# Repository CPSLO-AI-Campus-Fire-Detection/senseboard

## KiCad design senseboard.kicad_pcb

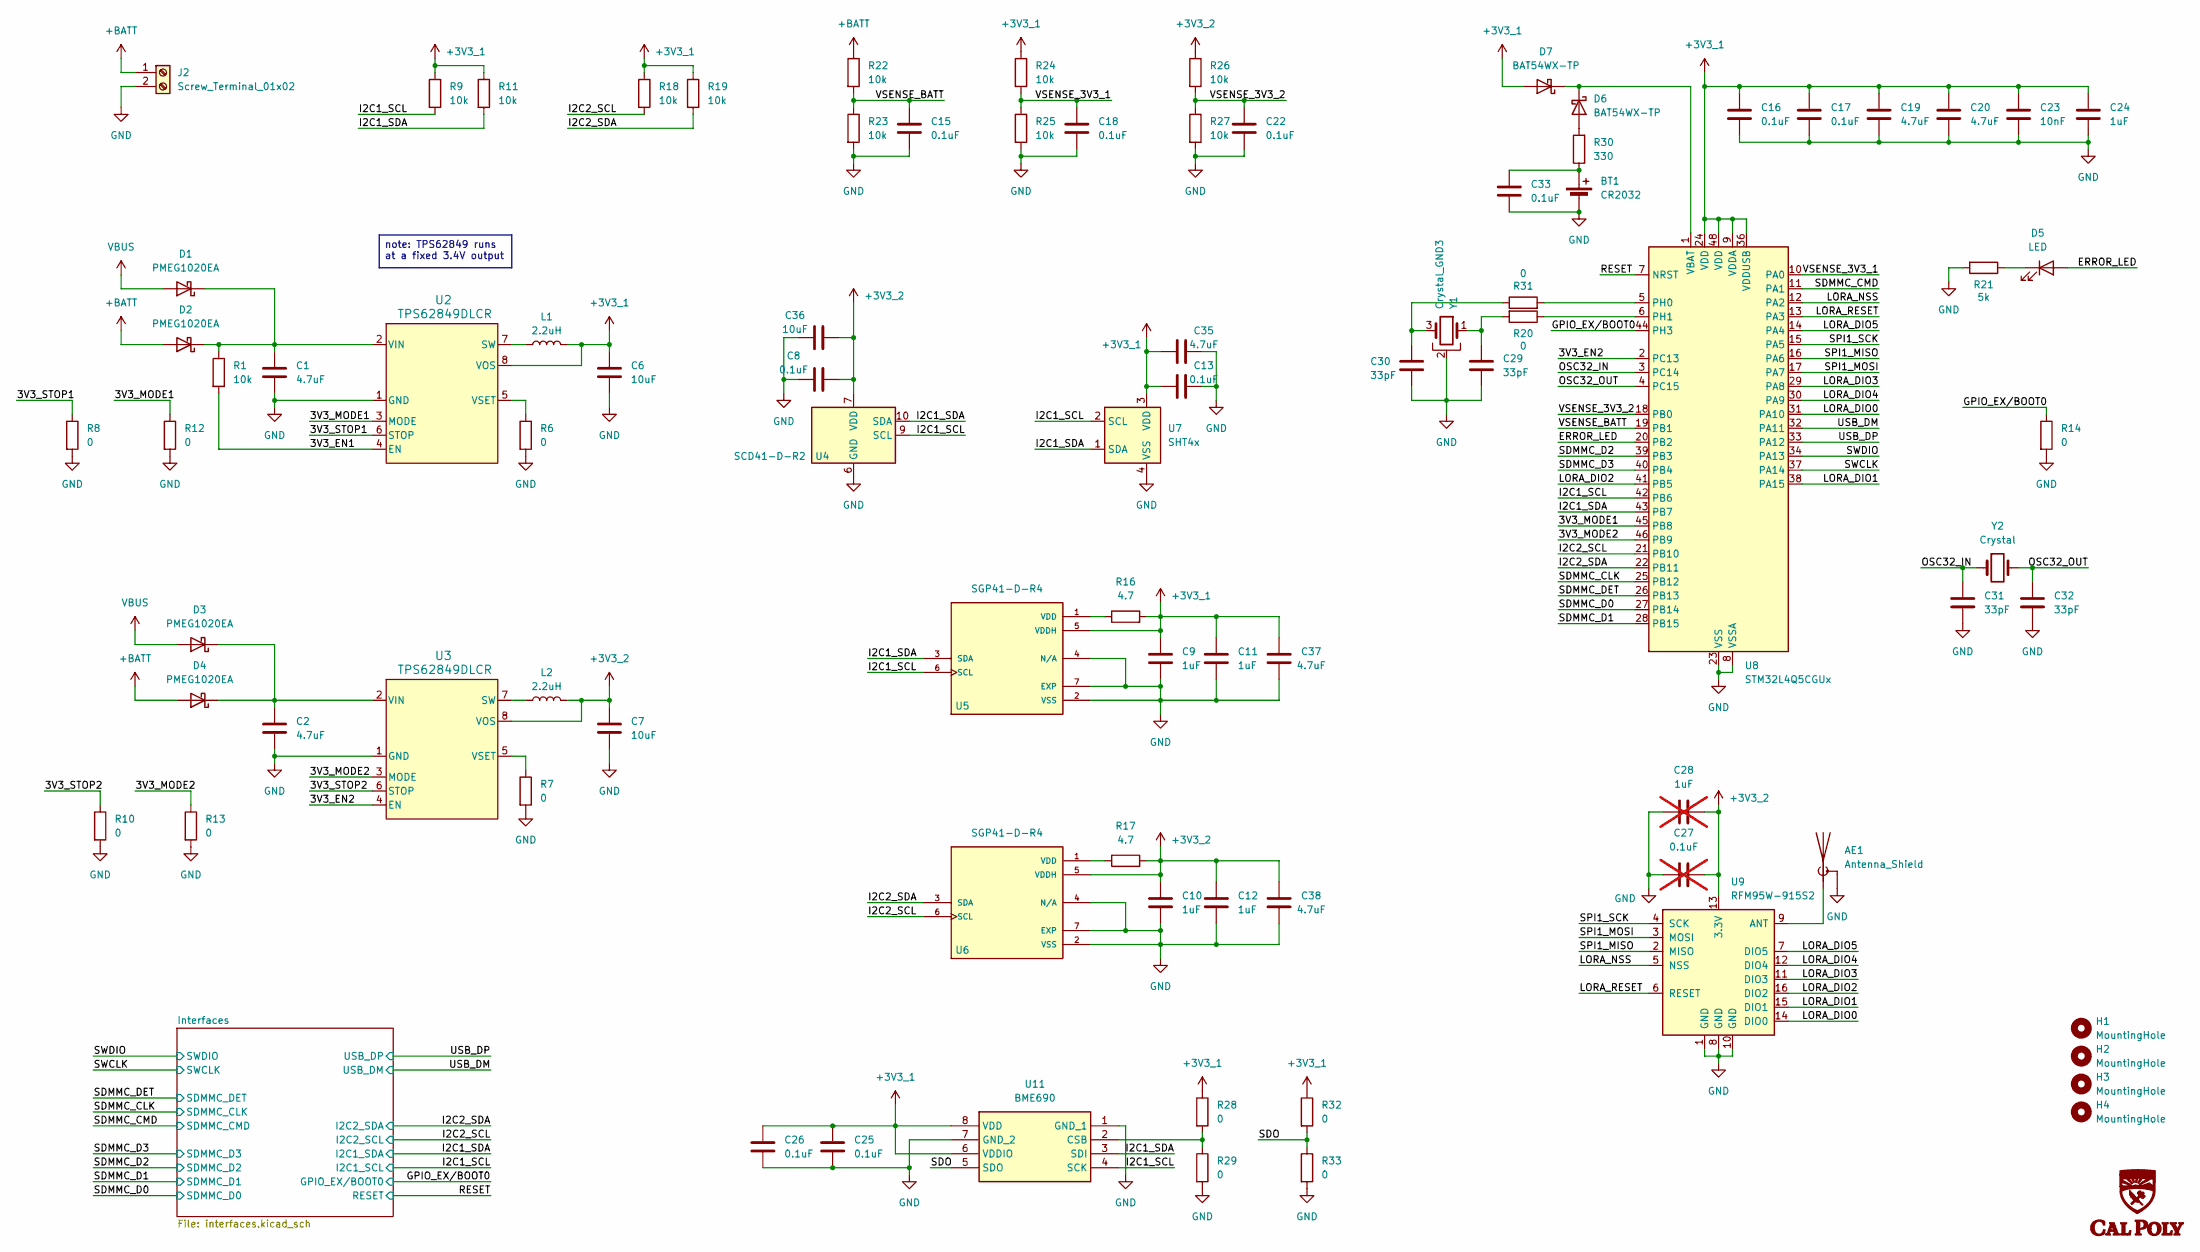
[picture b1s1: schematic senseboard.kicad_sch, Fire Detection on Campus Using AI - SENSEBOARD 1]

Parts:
AE1: Antenna_Shield; SMA_Molex_73251-1153_EdgeMount_Horizontal
BT1: CR2032; BatteryHolder_Keystone_1057_1x2032
C1, C2: 4.7uF; C_0805_2012Metric
C6, C7, C36: 10uF; C_0805_2012Metric
C8, C13, C15, C16, C17, C18, C22, C25, C26, C33: 0.1uF; C_0402_1005Metric
C9, C10, C11, C12, C24: 1uF; C_0603_1608Metric
C19, C20, C35, C37, C38: 4.7uF; C_0603_1608Metric
C23: 10nF; C_0402_1005Metric
C27: 0.1uF; C_0603_1608Metric; not fitted
C28: 1uF; C_0805_2012Metric; not fitted
C29, C30, C31, C32: 33pF; C_0402_1005Metric
D1, D3: PMEG1020EA; D_SMP_DO-220AA
D2, D4: PMEG1020EA; D_SMA
D5: LED; LED_0402_1005Metric
D6, D7: BAT54WX-TP; D_SOD-523
H1, H2, H3, H4: MountingHole; MountingHole_3.2mm_M3_ISO7380
J2: Screw_Terminal_01x02; JST_XH_B2B-XH-AM_1x02_P2.50mm_Vertical
L1, L2: 2.2uH; L_Murata_DFE201610P
R1, R9, R11, R18, R19, R22, R23, R24, R25, R26, R27: 10k; R_0402_1005Metric
R6, R7, R8, R10, R12, R13, R14, R20, R28, R29, R31, R32, R33: 0; R_0402_1005Metric
R16, R17: 4.7; R_0603_1608Metric
R21: 5k; R_0402_1005Metric
R30: 330; R_0603_1608Metric
U2, U3: TPS62849DLCR; VSON8_2P1X1P6_TEX
U4: SCD41-D-R2; Sensirion_SCD4x-1EP_10.1x10.1mm_P1.25mm_EP4.8x4.8mm
U5, U6: SGP41-D-R4; XDCR_SGP41-D-R4; PARTREV 1.0
U7: SHT4x; Sensirion_DFN-4_1.5x1.5mm_P0.8mm_SHT4x_NoCentralPad
U8: STM32L4Q5CGUx; QFN-48-1EP_7x7mm_P0.5mm_EP5.6x5.6mm
U9: RFM95W-915S2; HOPERF_RFM9XW_SMD
U11: BME690; Mouser Part Number 262-BME690
Y1: Crystal_GND3; Resonator_SMD_Murata_CSTxExxV-3Pin_3.0x1.1mm
Y2: Crystal; Crystal_SMD_EuroQuartz_EQ161-2Pin_3.2x1.5mm

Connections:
+3V3_1: C6.1, C9.2, C11.2, C13.2, C16.2, C17.2, C19.2, C20.2, C23.2, C24.2, C25.1, C26.1, C35.2, C37.1, D7.2 (A), L1.2, R9.1, R11.1, R16.2, R18.1, R19.1, R24.1, R28.1, R32.1, U2.8 (VOS), U5.5 (VDDH), U7.3 (VDD), U8.9 (VDDA), U8.24 (VDD), U8.36 (VDDUSB), U8.48 (VDD), U11.6 (VDDIO), U11.8 (VDD); also elsewhere on the board
+3V3_2: C7.1, C8.2, C10.2, C12.2, C27.1, C28.1, C36.2, C38.1, L2.2, R17.2, R26.1, U3.8 (VOS), U4.7 (VDD), U4.19 (VDD), U6.5 (VDDH), U9.13 (3.3V)
+BATT: D2.2 (A), D4.2 (A), J2.1, R22.1
/3V3_EN1: R1.2, U2.4 (EN)
/3V3_EN2: U3.4 (EN), U8.2 (PC13)
/3V3_MODE1: R12.1, U2.3 (MODE), U8.45 (PB8)
/3V3_MODE2: R13.1, U3.3 (MODE), U8.46 (PB9)
/3V3_STOP1: R8.1, U2.6 (STOP)
/3V3_STOP2: R10.1, U3.6 (STOP)
/ERROR_LED: D5.2 (A), U8.20 (PB2)
/GPIO_EX/BOOT0: R14.1, U8.44 (PH3); also elsewhere on the board
/I2C1_SCL: R9.2, U4.9 (SCL), U5.6 (SCL), U7.2 (SCL), U8.42 (PB6), U11.4 (SCK); also elsewhere on the board
/I2C1_SDA: R11.2, U4.10 (SDA), U5.3 (SDA), U7.1 (SDA), U8.43 (PB7), U11.3 (SDI); also elsewhere on the board
/I2C2_SCL: R18.2, U6.6 (SCL), U8.21 (PB10); also elsewhere on the board
/I2C2_SDA: R19.2, U6.3 (SDA), U8.22 (PB11); also elsewhere on the board
/LORA_DIO0: U8.31 (PA10), U9.14 (DIO0)
/LORA_DIO1: U8.38 (PA15), U9.15 (DIO1)
/LORA_DIO2: U8.41 (PB5), U9.16 (DIO2)
/LORA_DIO3: U8.29 (PA8), U9.11 (DIO3)
/LORA_DIO4: U8.30 (PA9), U9.12 (DIO4)
/LORA_DIO5: U8.14 (PA4), U9.7 (DIO5)
/LORA_NSS: U8.12 (PA2), U9.5 (NSS)
/LORA_RESET: U8.13 (PA3), U9.6 (RESET)
/OSC32_IN: C31.1, U8.3 (PC14), Y2.1
/OSC32_OUT: C32.1, U8.4 (PC15), Y2.2
/RESET: U8.7 (NRST); also elsewhere on the board
/SDMMC_CLK: U8.25 (PB12); also elsewhere on the board
/SDMMC_CMD: U8.11 (PA1); also elsewhere on the board
/SDMMC_D0: U8.27 (PB14); also elsewhere on the board
/SDMMC_D1: U8.28 (PB15); also elsewhere on the board
/SDMMC_D2: U8.39 (PB3); also elsewhere on the board
/SDMMC_D3: U8.40 (PB4); also elsewhere on the board
/SDMMC_DET: U8.26 (PB13); also elsewhere on the board
/SDO: R32.2, R33.1, U11.5 (SDO)
/SPI1_MISO: U8.16 (PA6), U9.2 (MISO)
/SPI1_MOSI: U8.17 (PA7), U9.3 (MOSI)
/SPI1_SCK: U8.15 (PA5), U9.4 (SCK)
/SWCLK: U8.37 (PA14); also elsewhere on the board
/SWDIO: U8.34 (PA13); also elsewhere on the board
/USB_DM: U8.32 (PA11); also elsewhere on the board
/USB_DP: U8.33 (PA12); also elsewhere on the board
/VSENSE_3V3_1: C18.1, R24.2, R25.1, U8.10 (PA0)
/VSENSE_3V3_2: C22.1, R26.2, R27.1, U8.18 (PB0)
/VSENSE_BATT: C15.1, R22.2, R23.1, U8.19 (PB1)
GND: AE1.2 (Shield), BT1.2 (-), C1.2, C2.2, C6.2, C7.2, C8.1, C9.1, C10.1, C11.1, C12.1, C13.1, C15.2, C16.1, C17.1, C18.2, C19.1, C20.1, C22.2, C23.1, C24.1, C25.2, C26.2, C27.2, C28.2, C29.2, C30.1, C31.2, C32.2, C33.1, C35.1, C36.1, C37.2, C38.2, J2.2, R6.2, R7.2, R8.2, R10.2, R12.2, R13.2, R14.2, R21.2, R23.2, R25.2, R27.2, R29.2, R33.2, U2.1 (GND), U3.1 (GND), U4.6 (GND), U4.20 (GND), U4.21 (GND), U5.2 (VSS), U5.4 (N/A), U5.7 (EXP), U6.2 (VSS), U6.4 (N/A), U6.7 (EXP), U7.4 (VSS), U8.8 (VSSA), U8.23 (VSS), U8.35 (VSS), U8.47 (VSS), U8.49 (VSS), U9.1 (GND), U9.8 (GND), U9.10 (GND), U11.1 (GND_1), U11.7 (GND_2), Y1.2; also elsewhere on the board
unnamed: AE1.1 (A), U9.9 (ANT)
unnamed: BT1.1 (+), C33.2, R30.1
unnamed: C29.1, R20.2, Y1.1
unnamed: C30.2, R31.1, Y1.3
unnamed: C1.1, D1.1 (K), D2.1 (K), R1.1, U2.2 (VIN)
unnamed: C2.1, D3.1 (K), D4.1 (K), U3.2 (VIN)
unnamed: D5.1 (K), R21.1
unnamed: D6.2 (A), R30.2
unnamed: D6.1 (K), D7.1 (K), U8.1 (VBAT)
unnamed: L1.1, U2.7 (SW)
unnamed: R6.1, U2.5 (VSET)
unnamed: L2.1, U3.7 (SW)
unnamed: R7.1, U3.5 (VSET)
unnamed: R16.1, U5.1 (VDD)
unnamed: R17.1, U6.1 (VDD)
unnamed: R31.2, U8.5 (PH0)
unnamed: R20.1, U8.6 (PH1)
unnamed: R28.2, R29.1, U11.2 (CSB)
VBUS: D1.2 (A), D3.2 (A); also elsewhere on the board

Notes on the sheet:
note: TPS62849 runs at a fixed 3.4V output

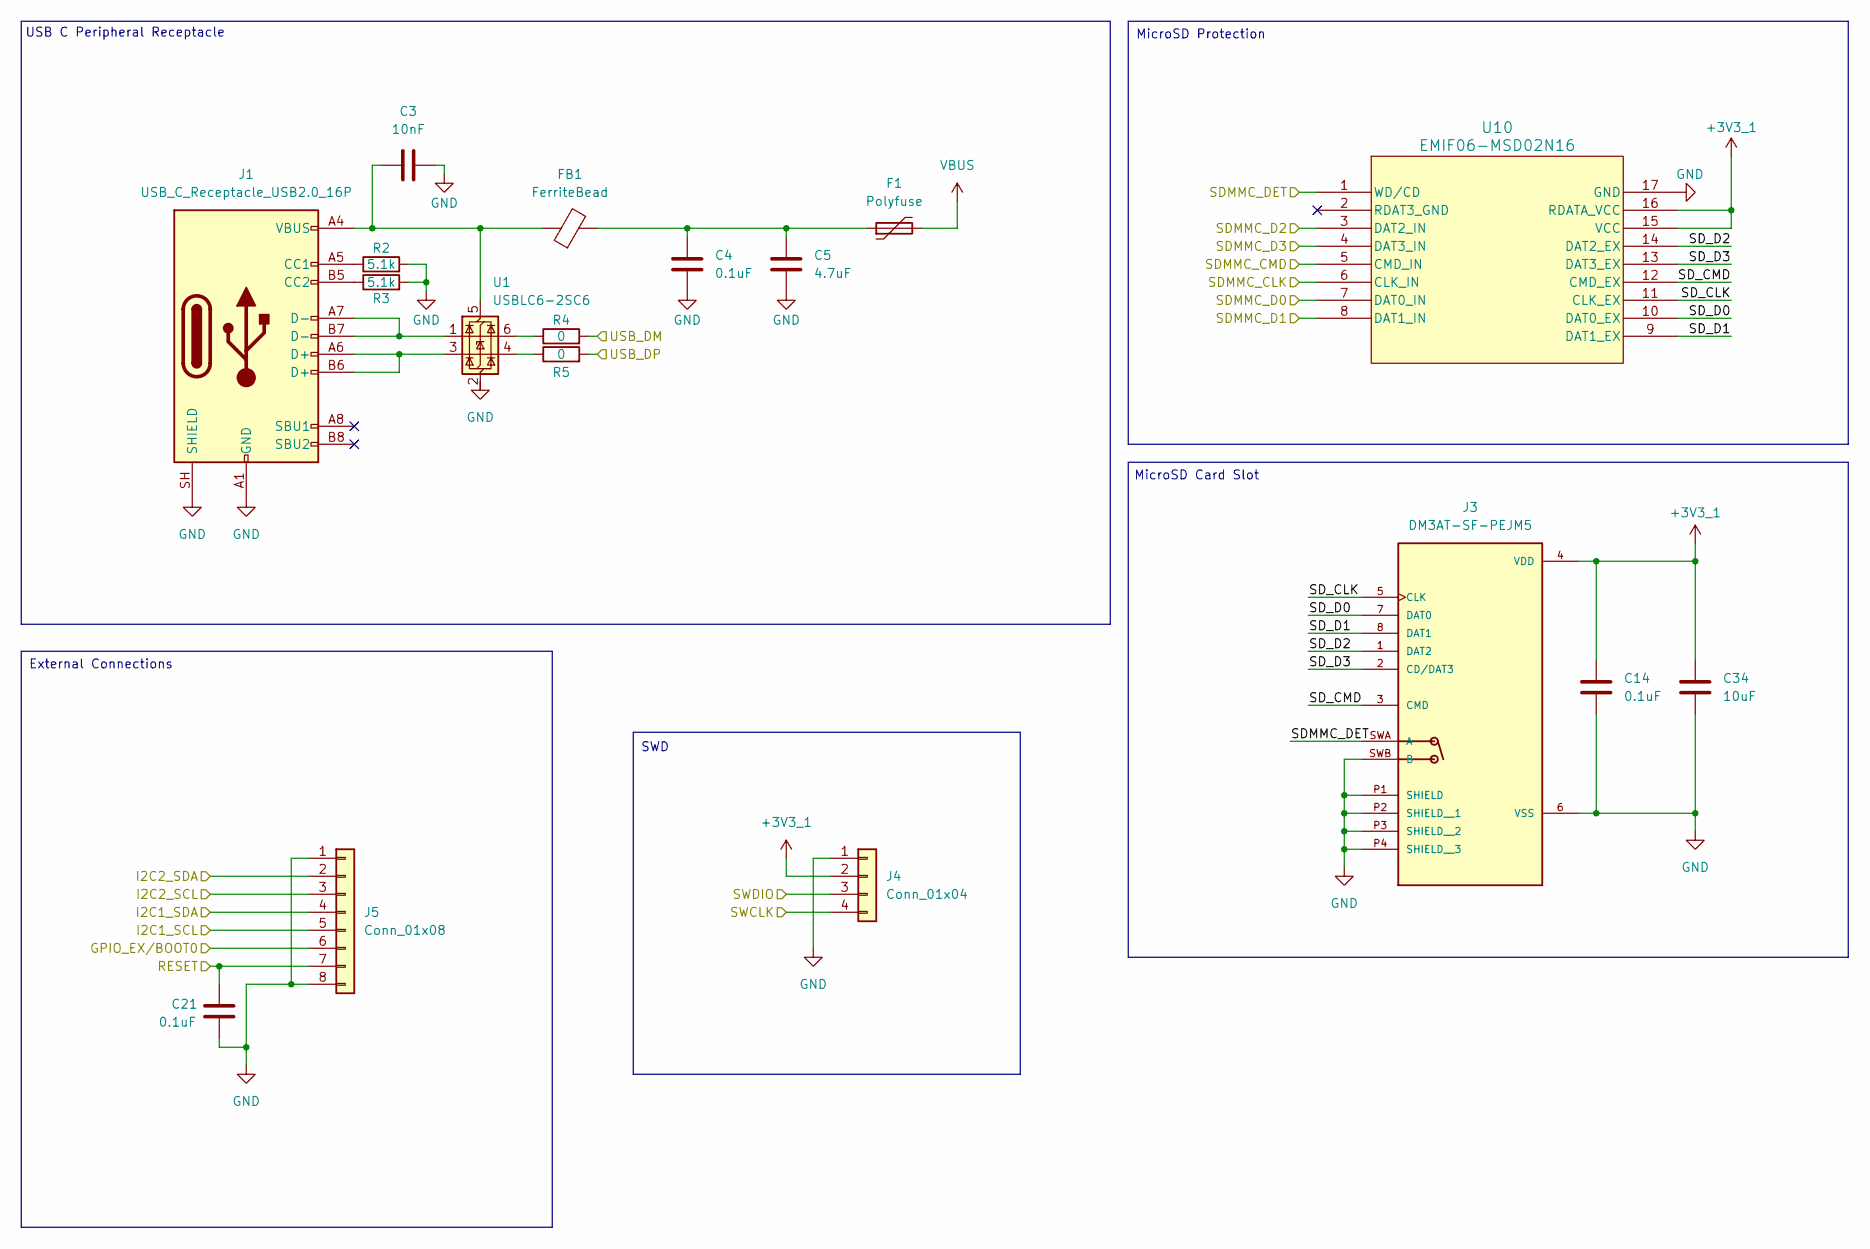
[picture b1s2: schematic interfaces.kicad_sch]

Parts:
C3: 10nF; C_0402_1005Metric
C4, C14, C21: 0.1uF; C_0402_1005Metric
C5: 4.7uF; C_0805_2012Metric
C34: 10uF; C_0805_2012Metric
F1: Polyfuse; Fuse_0805_2012Metric
FB1: FerriteBead; L_0603_1608Metric
J1: USB_C_Receptacle_USB2.0_16P; USB_C_Receptacle_G-Switch_GT-USB-7010ASV
J3: DM3AT-SF-PEJM5; HRS_DM3AT-SF-PEJM5; PARTREV 20200913
J4: Conn_01x04; PinHeader_1x04_P2.54mm_Vertical
J5: Conn_01x08; PinHeader_1x08_P2.54mm_Vertical
R2, R3: 5.1k; R_0402_1005Metric
R4, R5: 0; R_0402_1005Metric
U1: USBLC6-2SC6; SOT-23-6
U10: EMIF06-MSD02N16; MICROQFN16_1P25X3P55X0P4_STM

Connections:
+3V3_1: C14.1, C34.1, J3.4 (VDD), J4.2, U10.15 (VCC), U10.16 (RDATA_VCC); also elsewhere on the board
/GPIO_EX/BOOT0: J5.6; also elsewhere on the board
/I2C1_SCL: J5.5; also elsewhere on the board
/I2C1_SDA: J5.4; also elsewhere on the board
/I2C2_SCL: J5.3; also elsewhere on the board
/I2C2_SDA: J5.2; also elsewhere on the board
/Interfaces/SD_CLK: J3.5 (CLK), U10.11 (CLK_EX)
/Interfaces/SD_CMD: J3.3 (CMD), U10.12 (CMD_EX)
/Interfaces/SD_D0: J3.7 (DAT0), U10.10 (DAT0_EX)
/Interfaces/SD_D1: J3.8 (DAT1), U10.9 (DAT1_EX)
/Interfaces/SD_D2: J3.1 (DAT2), U10.14 (DAT2_EX)
/Interfaces/SD_D3: J3.2 (CD/DAT3), U10.13 (DAT3_EX)
/RESET: C21.1, J5.7; also elsewhere on the board
/SDMMC_CLK: U10.6 (CLK_IN); also elsewhere on the board
/SDMMC_CMD: U10.5 (CMD_IN); also elsewhere on the board
/SDMMC_D0: U10.7 (DAT0_IN); also elsewhere on the board
/SDMMC_D1: U10.8 (DAT1_IN); also elsewhere on the board
/SDMMC_D2: U10.3 (DAT2_IN); also elsewhere on the board
/SDMMC_D3: U10.4 (DAT3_IN); also elsewhere on the board
/SDMMC_DET: J3.SWA (A), U10.1 (WD/CD); also elsewhere on the board
/SWCLK: J4.4; also elsewhere on the board
/SWDIO: J4.3; also elsewhere on the board
/USB_DM: R4.2; also elsewhere on the board
/USB_DP: R5.2; also elsewhere on the board
GND: C3.2, C4.1, C5.1, C14.2, C21.2, C34.2, J1.A1 (GND), J1.A12 (GND), J1.B1 (GND), J1.B12 (GND), J1.SH (SHIELD), J3.6 (VSS), J3.P1 (SHIELD), J3.P2 (SHIELD__1), J3.P3 (SHIELD__2), J3.P4 (SHIELD__3), J3.SWB (B), J4.1, J5.1, J5.8, R2.2, R3.2, U10.17 (GND); also elsewhere on the board
unnamed: C4.2, C5.2, F1.1, FB1.2
unnamed: J1.A5 (CC1), R2.1
unnamed: J1.B5 (CC2), R3.1
unnamed: J1.A6 (D+), J1.B6 (D+), U1.3 (I/O2)
unnamed: J1.A7 (D-), J1.B7 (D-), U1.1 (I/O1)
unnamed: R4.1, U1.6 (I/O1)
unnamed: R5.1, U1.4 (I/O2)
unnamed: C3.1, FB1.1, J1.A4 (VBUS), J1.A9 (VBUS), J1.B4 (VBUS), J1.B9 (VBUS), U1.5 (VBUS)
VBUS: F1.2; also elsewhere on the board

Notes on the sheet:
External Connections
SWD
MicroSD Card Slot
MicroSD Protection
USB C Peripheral Receptacle

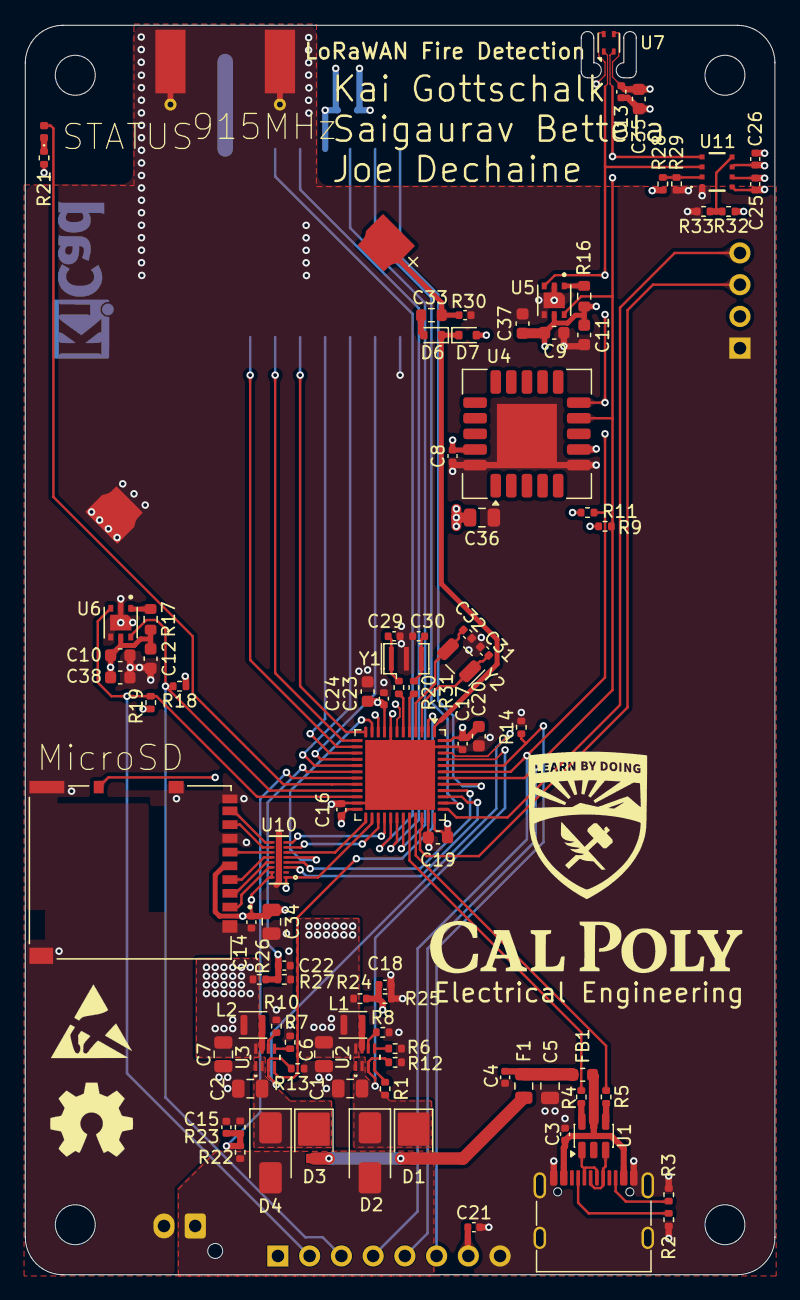
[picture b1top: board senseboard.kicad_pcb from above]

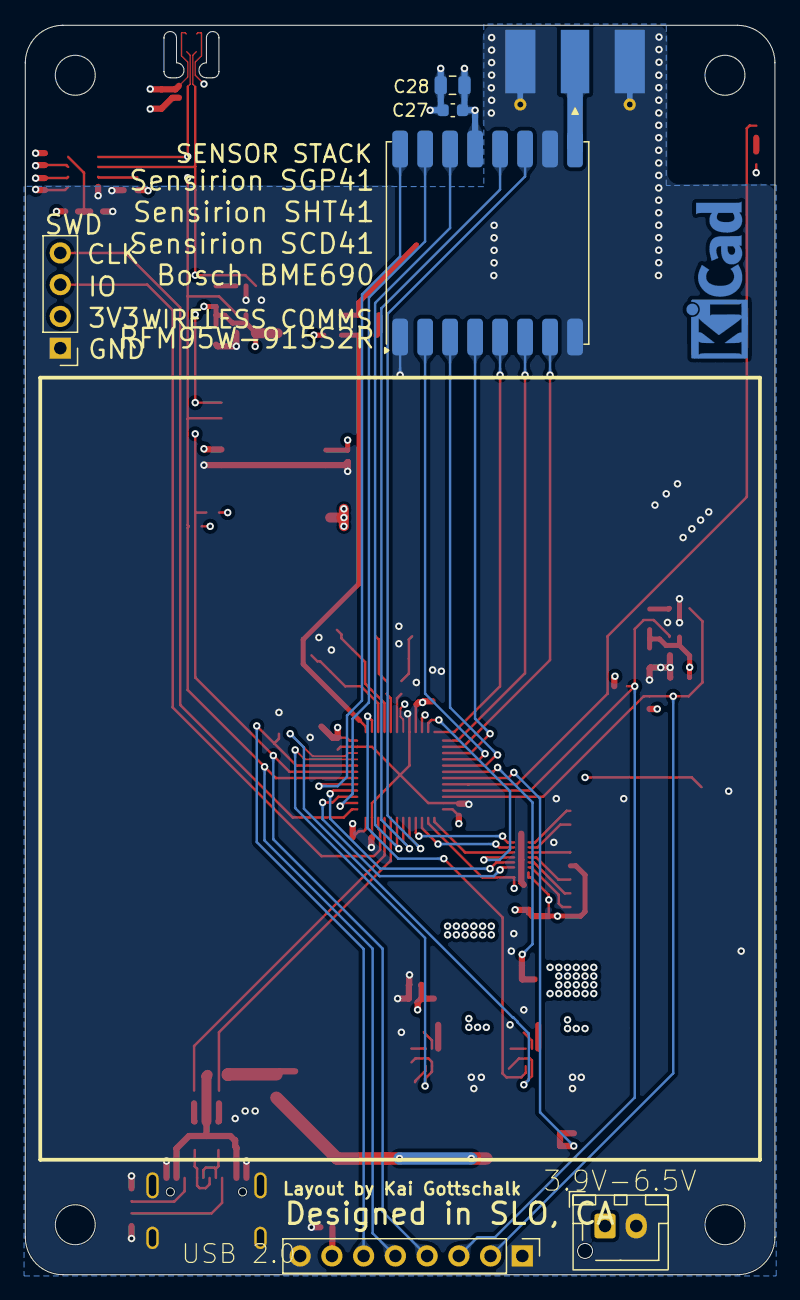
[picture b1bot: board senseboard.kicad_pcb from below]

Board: 6 copper layers, 60.0 x 100.0 mm, 105 parts (7 on the bottom side), 78 nets.

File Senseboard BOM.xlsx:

Value | Reference | Footprint | JLCPCB Part # | Qty | MFR | PN | DNP
DNP | AE1 | Connector_Coaxial:SMA_Molex_73251-1153_EdgeMount_Horizontal | DNP | 1 | Molex | 732511153 | DNP
DNP | BT1 | Battery:BatteryHolder_Keystone_1057_1x2032 | DNP | 1 | Keystone Electronics | 1057
4.7uF | C1,C2,C5 | Capacitor_SMD:C_0805_2012Metric | C1779 | 3 | Samsung Electro-Mechanics | CL21A475KAQNNNE
10nF | C3,C23 | Capacitor_SMD:C_0402_1005Metric | C327009 | 2 | Murata Electronics | GRM155R71C103KA01D
0.1uF | C4,C8,C13,C14,C15,C16,C17,C18,C21,C22,C25,C26,C33 | Capacitor_SMD:C_0402_1005Metric | C133086 | 13 | Samsung Electro-Mechanics | CL05B104KP5NNNC
10uF | C6,C7,C34,C36 | Capacitor_SMD:C_0805_2012Metric | C1713 | 4 | Samsung Electro-Mechanics | CL21A106KOQNNNE
1uF | C9,C10,C11,C12,C24 | Capacitor_SMD:C_0603_1608Metric | C29936 | 5 | Samsung Electro-Mechanics | CL10B105KA8NNNC
4.7uF | C19,C20,C35,C37,C38 | Capacitor_SMD:C_0603_1608Metric | C1705 | 5 | Samsung Electro-Mechanics | CL10A475KP8NNNC
DNP | C27 | Capacitor_SMD:C_0603_1608Metric |  | 1 | KEMET | C0603C104K3RACTU | DNP
DNP | C28 | Capacitor_SMD:C_0805_2012Metric |  | 1 | Samsung Electro-Mechanics | CL21A475KAQNNNE | DNP
DNP | C29,C30 | Capacitor_SMD:C_0402_1005Metric |  | 2 |  |  | DNP
7pF | C31,C32 | Capacitor_SMD:C_0402_1005Metric | C161333 | 2 | Murata Electronics | GRM1555C1H7R0CA01D
STPS120MF | D1,D3 | Diode_SMD:D_SMP_DO-220AA | C2927425 | 2 | STMicroelectronics | STPS120MF
STPS1L30A | D2,D4 | Diode_SMD:D_SMA | C157388 | 2 | STMicroelectronics | STPS1L30A
LED | D5 | LED_SMD:LED_0402_1005Metric | C364556 | 1 | Lite-On Inc. | LTST-C281KRKT
BAT54WX-TP | D6,D7 | Diode_SMD:D_SOD-523 | C283259 | 2 | MCC (Micro Commercial Components) | BAT54WX-TP
Polyfuse | F1 | Fuse:Fuse_0805_2012Metric | C5220829 | 1 | Bel Fuse Inc. | 0ZCK0050FF2E
FerriteBead | FB1 | Inductor_SMD:L_0603_1608Metric | C107335 | 1 | TDK | MPZ1608S601ATA00
USB_C_Receptacle_USB2.0_16P | J1 | Connector_USB:USB_C_Receptacle_G-Switch_GT-USB-7010ASV | C2988369 | 1 | G-Switch | GT-USB-7010ASV
DNP | J2 | Connector_JST:JST_XH_B2B-XH-AM_1x02_P2.50mm_Vertical |  | 1 | JST Sales America Inc. | B2B-XH-AM | DNP
DM3AT-SF-PEJM5 | J3 | DM3AT_SF_PEJM5:HRS_DM3AT-SF-PEJM5 | C114218 | 1 | Hirose Electric Co Ltd | DM3AT-SF-PEJM5
DNP | J4 | Connector_PinHeader_2.54mm:PinHeader_1x04_P2.54mm_Vertical |  | 1 |  |  | DNP
DNP | J5 | Connector_PinHeader_2.54mm:PinHeader_1x08_P2.54mm_Vertical |  | 1 |  |  | DNP
2.2uH | L1,L2 | Inductor_SMD:L_Murata_DFE201610P | C337893 | 2 | Murata Electronics | DFE201612E-2R2M=P2
10k | R1,R9,R11,R18,R19 | Resistor_SMD:R_0402_1005Metric | C60490 | 5 | YAGEO | RC0402FR-0710KL
5.1k | R2,R3 | Resistor_SMD:R_0402_1005Metric | C278598 | 2 | Panasonic Industry | ERJ-2RKF5101X
0 | R4,R5,R6,R7,R8,R10,R20,R28,R31,R33 | Resistor_SMD:R_0402_1005Metric | C60485 | 10 | YAGEO | RC0402JR-070RL
100k | R12,R13,R14 | Resistor_SMD:R_0402_1005Metric | C60491 | 3 | YAGEO | RC0402FR-07100KL
4.7 | R16,R17 | Resistor_SMD:R_0603_1608Metric | C5549523 | 2 | YAGEO | RC0603FR-134R7L
330 | R21 | Resistor_SMD:R_0402_1005Metric | C226996 | 1 | YAGEO | AC0402FR-07330RL
47k | R22,R23,R24,R25,R26,R27 | Resistor_SMD:R_0402_1005Metric | C728561 | 6 | YAGEO | RT0402BRD0747KL
DNP | R29,R32 | Resistor_SMD:R_0402_1005Metric |  | 2 | YAGEO | RC0402JR-070RL | DNP
330 | R30 | Resistor_SMD:R_0603_1608Metric | C105881 | 1 | YAGEO | RC0603FR-07330RL
USBLC6-2SC6 | U1 | Package_TO_SOT_SMD:SOT-23-6 | C7519 | 1 | STMicroelectronics | USBLC6-2SC6
TPS62849DLCR | U2,U3 | TPS62849DLCR:VSON8_2P1X1P6_TEX | C2071003 | 2 | Texas Instruments | TPS62849DLCR
SCD41-D-R2 | U4 | Sensor:Sensirion_SCD4x-1EP_10.1x10.1mm_P1.25mm_EP4.8x4.8mm | C3659294 | 1 | Sensirion AG | SCD41-D-R2
SGP41-D-R4 | U5,U6 | SGP41-D-R4:XDCR_SGP41-D-R4 | C3659325 | 2 | Sensirion AG | SGP41-D-R4
SHT4x | U7 | Sensor_Humidity:Sensirion_DFN-4_1.5x1.5mm_P0.8mm_SHT4x_NoCentralPad | C7461863 | 1 | Sensirion AG | SHT41A-FD1B-R2
STM32L4Q5CGUx | U8 | Package_DFN_QFN:QFN-48-1EP_7x7mm_P0.5mm_EP5.6x5.6mm | C2970026 | 1 | STMicroelectronics | STM32L4P5CGU6
DNP | U9 | RF_Module:HOPERF_RFM9XW_SMD |  | 1 | RF Solutions | RFM95W-915S2 | DNP
EMIF06-MSD02N16 | U10 | EMIF06_MSD02N16:MICROQFN16_1P25X3P55X0P4_STM | C5267594 | 1 | STMicroelectronics | EMIF06-MSD02N16
BME690 | U11 | BME690:BME690 | C42431867 | 1 | Bosch Sensortec | BME690
Crystal_GND3 | Y1 | Crystal:Resonator_SMD_Murata_CSTxExxV-3Pin_3.0x1.1mm | C341520 | 1 | Murata Electronics | CSTNE12M0G550000R0
Crystal | Y2 | Crystal:Crystal_SMD_EuroQuartz_EQ161-2Pin_3.2x1.5mm | C276424 | 1 | Abracon LLC | ABS07-32.768KHZ-7-T

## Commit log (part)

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2026-04-20 created project and added initial ICs in schematic design
2026-04-25 added updated regulators, power domains
2026-04-27 changed sheet size, added redundant sgp and worked to set up power domains further
2026-04-29 added LORA module, sd card, usb c filtering, stm32 neccesary reset/clocks and added ADC dividers and i2c pull ups
2026-04-29 adjusted file structure for kicad 10
2026-04-29 added initial bom
2026-04-30 fixed gnd positioning and added error led
2026-05-02 minor changes to schematic, modified sd card holder and added all footprint references, began layout of board
2026-05-03 added sd card protection, completed most layout, added bosch sensor, graphics
2026-05-03 connected n/a on sgp41 to gnd
2026-05-03 added values and variant for assembly, added 3d model for sd protection to layout, played with via setup
2026-05-05 added blocking protection for coin cell and charge limiting
2026-05-06 added lots of additional resistors and caps for added decoupling and modification if neccesary, finalized layout and added graphics
2026-05-06 final layout mods and added a couple more bulk caps
2026-05-06 finalized schematic placement and exported updated BOM, changed 50k to 47k
2026-05-07 added first turn of gerbers and drill files, added boms and placement files
2026-05-17 final turn gerbers
